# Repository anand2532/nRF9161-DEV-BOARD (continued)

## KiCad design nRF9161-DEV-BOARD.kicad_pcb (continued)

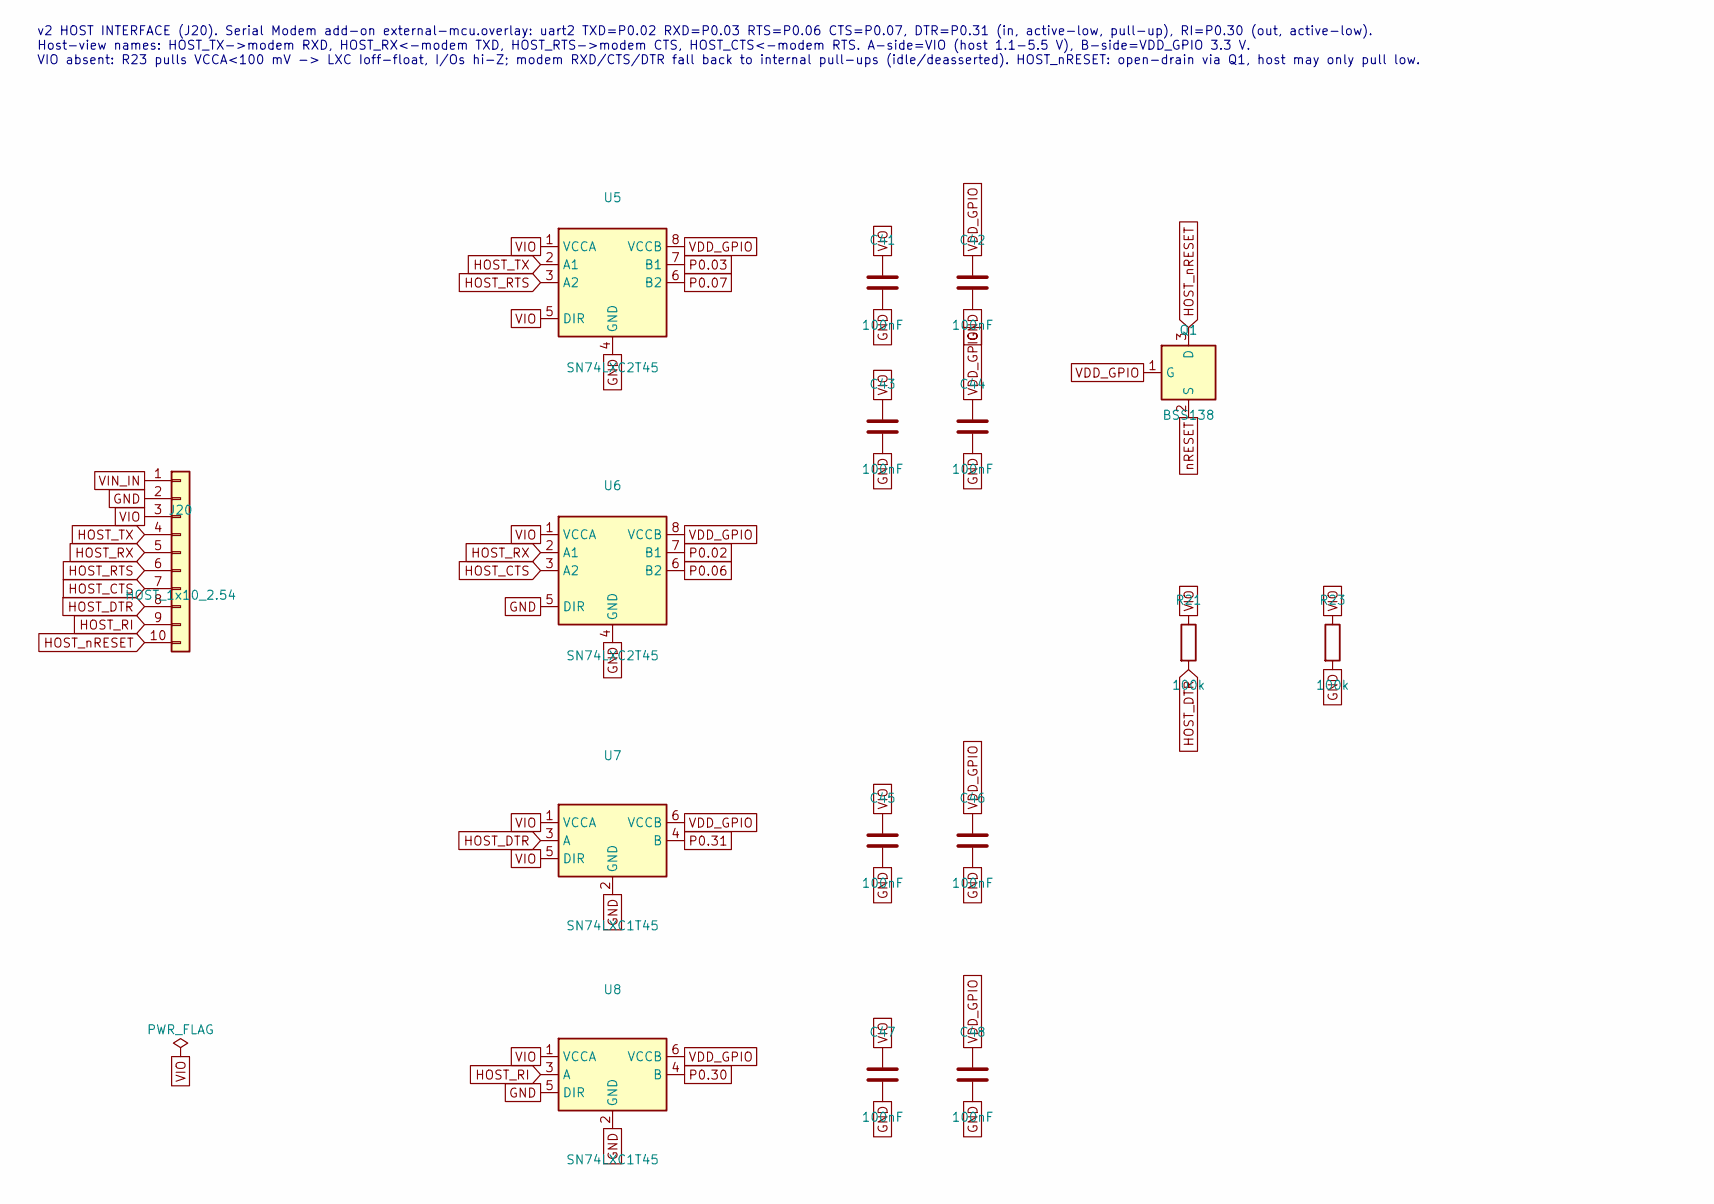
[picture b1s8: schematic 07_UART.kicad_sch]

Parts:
C41, C42, C43, C44, C45, C46, C47, C48: 100nF; C_0402_1005Metric; MPN CL05B104KO5NNNC; LCSC C1525
J20: HOST_1x10_2.54; PinHeader_1x10_P2.54mm_Vertical; MPN 2.54-1*10P; LCSC C57369
Q1: BSS138; SOT-23; MPN BSS138; LCSC C52895
R21, R23: 100k; R_0402_1005Metric; MPN 0402WGF1003TCE; LCSC C25741
U5, U6: SN74LXC2T45; VSSOP-8_2.3x2mm_P0.5mm; MPN SN74LXC2T45DCUR; LCSC C5217891
U7, U8: SN74LXC1T45; SOT-23-6; MPN SN74LXC1T45DBVR; LCSC C4364198

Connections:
GND: C41.2, C42.2, C43.2, C44.2, C45.2, C46.2, C47.2, C48.2, J20.2, R23.2, U5.4 (GND), U6.4 (GND), U6.5 (DIR), U7.2 (GND), U8.2 (GND), U8.5 (DIR); also elsewhere on the board
HOST_CTS: J20.7, U6.3 (A2)
HOST_DTR: J20.8, R21.2, U7.3 (A)
HOST_RI: J20.9, U8.3 (A)
HOST_RTS: J20.6, U5.3 (A2)
HOST_RX: J20.5, U6.2 (A1)
HOST_TX: J20.4, U5.2 (A1)
HOST_nRESET: J20.10, Q1.3 (D)
P0.02: U6.7 (B1); also elsewhere on the board
P0.03: U5.7 (B1); also elsewhere on the board
P0.06: U6.6 (B2); also elsewhere on the board
P0.07: U5.6 (B2); also elsewhere on the board
P0.30: U8.4 (B); also elsewhere on the board
P0.31: U7.4 (B); also elsewhere on the board
VDD_GPIO: C42.1, C44.1, C46.1, C48.1, Q1.1 (G), U5.8 (VCCB), U6.8 (VCCB), U7.6 (VCCB), U8.6 (VCCB); also elsewhere on the board
VIN_IN: J20.1; also elsewhere on the board
VIO: C41.1, C43.1, C45.1, C47.1, J20.3, R21.1, R23.1, U5.1 (VCCA), U5.5 (DIR), U6.1 (VCCA), U7.1 (VCCA), U7.5 (DIR), U8.1 (VCCA)
nRESET: Q1.2 (S); also elsewhere on the board

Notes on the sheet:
v2 HOST INTERFACE (J20). Serial Modem add-on external-mcu.overlay: uart2 TXD=P0.02 RXD=P0.03 RTS=P0.06 CTS=P0.07, DTR=P0.31 (in, active-low, pull-up), RI=P0.30 (out, active-low). Host-view names: HOST_TX->modem RXD, HOST_RX<-modem TXD, HOST_RTS->modem CTS, HOST_CTS<-modem RTS. A-side=VIO (host 1.1-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

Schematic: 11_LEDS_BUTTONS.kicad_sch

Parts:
D4: Green LED; LED_0603_1608Metric; MPN LTST-C191KGKT; LCSC C125098
R10: 1k; R_0402_1005Metric; MPN 0402WGF1001TCE; LCSC C11702

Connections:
GND: D4.2 (A); also elsewhere on the board
LED1_A: D4.1 (K), R10.2
P0.00: R10.1; also elsewhere on the board

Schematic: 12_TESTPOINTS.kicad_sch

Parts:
TP13: VDD_GPIO; TestPoint_Pad_D1.5mm
TP14: VDD_nRF; TestPoint_Pad_D1.5mm
TP15: VIN; TestPoint_Pad_D1.5mm
TP16: GND; TestPoint_Pad_D1.5mm
TP17: ENABLE; TestPoint_Pad_D1.5mm

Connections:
ENABLE: TP17.1; also elsewhere on the board
GND: TP16.1; also elsewhere on the board
VDD_GPIO: TP13.1; also elsewhere on the board
VDD_nRF: TP14.1; also elsewhere on the board
VIN: TP15.1; also elsewhere on the board

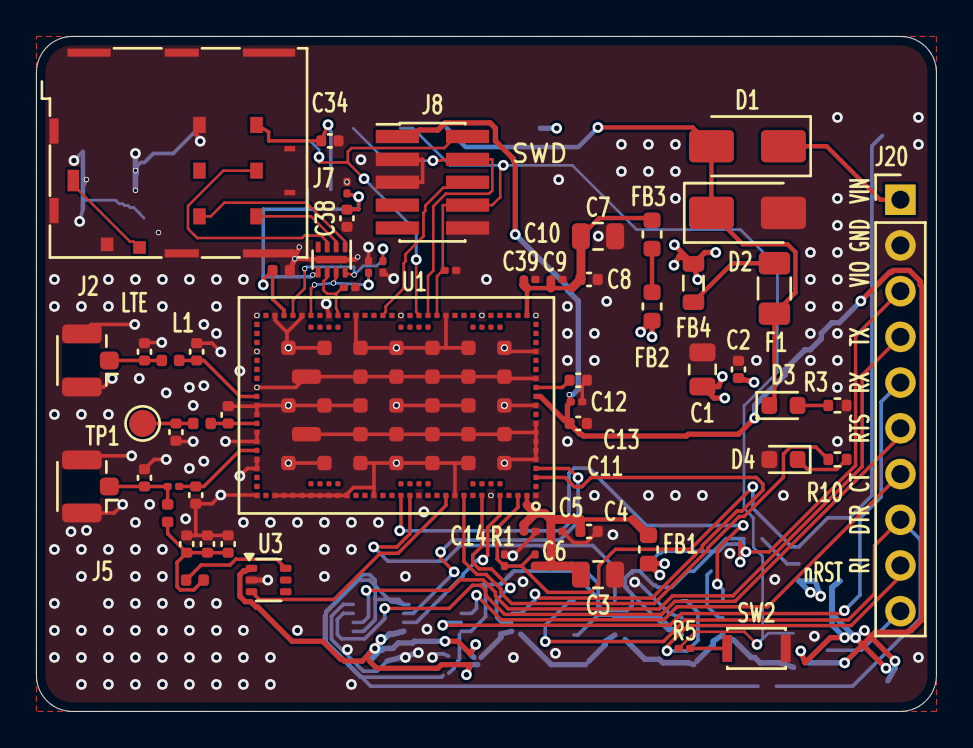
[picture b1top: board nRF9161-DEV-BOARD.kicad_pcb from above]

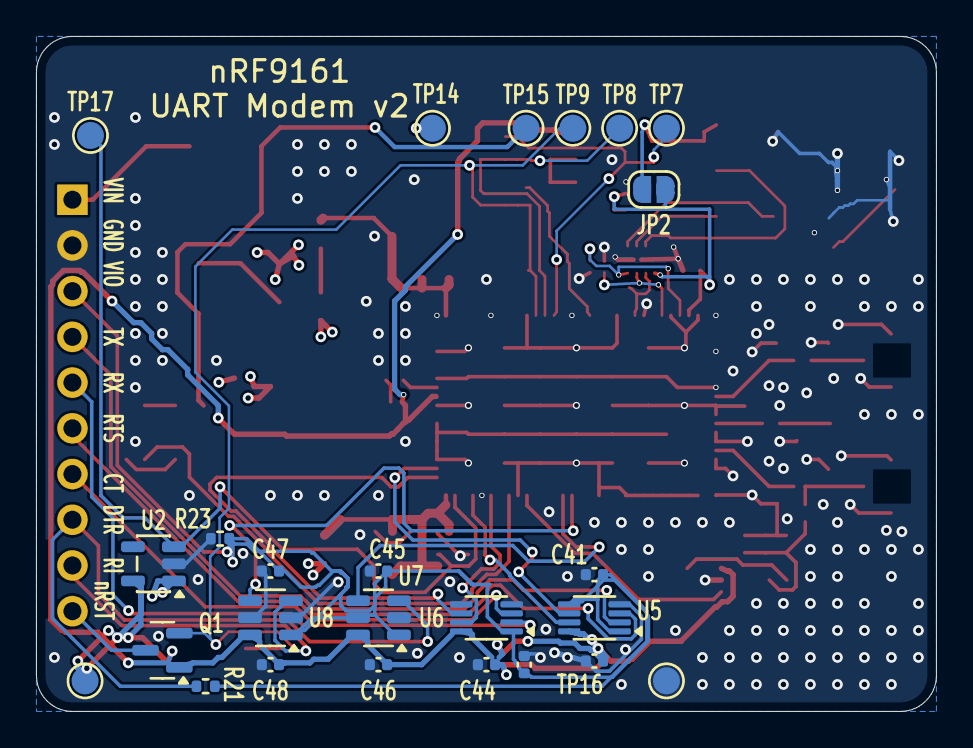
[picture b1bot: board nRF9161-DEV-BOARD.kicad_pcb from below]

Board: 4 copper layers, 50.0 x 37.5 mm, 84 parts (25 on the bottom side), 51 nets.

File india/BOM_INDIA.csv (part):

Ref,Qty/board,Value,Package,MPN,LCSC,V1 vendor,V1 URL,V1 INR/unit,V1 stock,V1 match,V2 vendor,V2 URL,V2 INR/unit,V2 stock,V2 match,Exact in-stock INR/board,Notes
U1,1,nRF9161 SiP,LGA 16.0x10.5,NRF9161-LACA-R7,C21547412,LionCircuits,https://www.lioncircuits.com/parts/NRF9161-LACA-R7,3745.04,In Stock (ships 7-10 d),exact,,,,,,3745.04,Not on Robu (only nRF9151-DK). Also try mouser.in / digikey.in.
U2,1,TLV73333P,SOT-23-5,TLV73333PDBVR,C134139,Robu,https://robu.in/product/tlv73333pdbvr-texas-instruments-300m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,20.0,In Stock,exact,,,,,,20.0,
U3,1,TPS22919,SC-70-6,TPS22919DCKR,C2149796,LionCircuits,https://www.lioncircuits.com/parts/TPS22919DCKR,29.31,In Stock (ships 7-10 d),exact,,,,,,29.31,Not on Robu. LionCircuits price tiers start at 10 pcs (₹19.62).
U4,1,TPD3F303,USON-8 DPV,TPD3F303DPVR,C2865991,LionCircuits,https://www.lioncircuits.com/parts/TPD3F303DPVR,200.1,In Stock (ships 7-10 d),exact,,,,,,200.1,Not on Robu.
"U5,U6",2,SN74LXC2T45,VSSOP-8,SN74LXC2T45DCUR,C5217891,Robu,https://robu.in/product/sn74lxc2t45dcur-texas-instruments-1-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,65.0,In Stock,exact,,,,,,130.0,
"U7,U8",2,SN74LXC1T45,SOT-23-6,SN74LXC1T45DBVR,C4364198,Robu,https://robu.in/product/sn74lxc1t45dbvr-texas-instruments-1-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,31.0,In Stock,exact,,,,,,62.0,
Q1,1,BSS138,SOT-23,BSS138 (onsemi),C52895,LionCircuits,https://www.lioncircuits.com/parts/BSS138,38.95,In Stock (ships 7-10 d),exact,Robu,https://robu.in/product/bss138-slkor-50v-220ma-3-5%cf%8910v2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,2.45,In Stock,equivalent,38.95,"Robu has Slkor BSS138 (same MPN, other maker). Lion manufacturer not verified on page."
C1,1,10uF 16V X5R,0805,CL21A106KOQNNNE,C1713,Robu,https://robu.in/product/cl21a106koqnnne-samsung-electro-mech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,1.5,In Stock,exact,LionCircuits,https://www.lioncircuits.com/parts/CL21A106KOQNNNE,14.72,In Stock,exact,1.5,
"C2,C30,C33,C41-C48",11,100nF,0402,CL05B104KO5NNNC,C1525,Robu,https://robu.in/product/cl05b104ko5nnnc-samsung-electro-mech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,0.1,In Stock,exact,,,,,,1.1,
"C3,C7",2,47uF 10V X5R,0805,GRM21BR61A476ME15L,C124129,Robu,https://robu.in/product/grm21br61a476me15k-murata-power-solu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,4.63,In Stock,equivalent,Robu (exact ME15L),https://robu.in/product/grm21br61a476me15l-murata-smd-multil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,11.0,Out of Stock,exact,,"ME15K = same part, different reel packaging suffix. Exact ME15L is OOS on Robu and LionCircuits (₹75.19 OOS)."
"C4,C8,C11,C13",4,4.7uF 10V X5R,0402,GRM155R61A475MEAAD,C335105,Robu,https://robu.in/product/grm155r61a475meaad-murata-smd-multil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,1.59,In Stock,exact,Robu,https://robu.in/product/cl05a475kp5nrnc-samsung-cap-ceramic-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,0.36,In Stock,equivalent,6.36,Backup: Samsung CL05A475KP5NRNC
"C5,C9,C12,C14",4,100nF 10V X5R,0201,GRM033R61A104KE15D,C76934,Robu,https://robu.in/product/grm033r61a104ke15d-murata-smd-multil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,1.2,In Stock,exact,Robu,https://robu.in/product/cl03a104ko3nnnc-samsang-16v-100nf-x5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,0.11,In Stock,equivalent,4.8,Backup: Samsung CL03A104KO3NNNC
"C6,C10",2,15pF 25V C0G,0201,GJM0335C1E150JB01D,C710722,LionCircuits,https://www.lioncircuits.com/parts/GJM0335C1E150JB01D,12.74,In Stock,exact,Robu,https://robu.in/product/grm0335c1h150ga01d-murata-electronic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,0.35,In Stock,equivalent,25.48,Robu backup GRM0335C1H150GA01D (not high-Q GJM).
C27,1,100pF C0G,0201,GRM0335C1H101JA01D,C76922,Robu,https://robu.in/product/grm0335c1h101ja01d-murata-cap-cerami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,0.68,In Stock,exact,,,,,,0.68,
C28,1,100pF,0402,GRM1555C1H101JA01D,C77177,Robu,https://robu.in/product/grm1555c1h101ja01d-murata-cap-cerami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,0.12,In Stock,exact,,,,,,0.12,
C29,1,10nF,0402,CL05B103KB5NNNC,C15195,Robu,https://robu.in/product/cl05b103kb5nnnc-samsung-electro-mech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,1.56,In Stock,exact,,,,,,1.56,
C34,1,220nF,0402,CL05B224KO5NNNC,C16772,Robu,https://robu.in/product/cl05b224ko5nnnc-samsung-electro-mech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,1.49,In Stock,exact,,,,,,1.49,
C35-C38,4,22pF C0G,0201,GRM0335C1H220JA01D,C76924,Robu,https://robu.in/product/grm0335c1h220ja01d-murata-cap-cerami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,0.68,In Stock,exact,,,,,,2.72,
C40,1,100nF 10V X7R,0402,GRM155R71A104KA01D,C71687,Robu,https://robu.in/product/grm155r71a104ka01d-murata-cap-cerami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,0.12,In Stock,exact,,,,,,0.12,
D1,1,SS34,SMA,SS34 (MDD),C8678,Robu,https://robu.in/product/ss34-mdd-40v-independent-3a-550mv3a-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,7.0,In Stock,exact,Robu,https://robu.in/product/ss34-slkor-40v-500mv3a-3a-smado-214a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,3.79,In Stock,equivalent,7.0,"Backup is Slkor SS34 (same MPN, other maker)."
D2,1,SMAJ5.0A,SMA,SMAJ5.0A,C10758,Robu,https://robu.in/product/smaj5-0a-littelfuse-smaj5-0a-tvs-dio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,21.0,In Stock,exact,LionCircuits,https://www.lioncircuits.com/parts/SMAJ5.0A,56.08,In Stock,exact,21.0,Robu part is Littelfuse (BOM maker RUILON); same MPN.
"D3,D4",2,Green LED,0603,LTST-C191KGKT,C125098,Robu,https://robu.in/product/ltst-c191kgkt-lite-on-20ma-35mcd-wat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,2.1,In Stock,exact,LionCircuits,https://www.lioncircuits.com/parts/LTST-C191KGKT,17.05,In Stock,exact,4.2,
F1,1,2A fuse,1206,0468002.NRHF,C187611,LionCircuits,https://www.lioncircuits.com/parts/0468002.NRHF,187.64,In Stock (ships 7-10 d),exact,Robu,https://robu.in/product/0466002-nr-littelfuse-0466002-nr-fus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,11.0,In Stock,equivalent,187.64,Robu backup 0466002.NR is very-fast-acting 2A 63V 1206 (0468 is slow-blow): check inrush.
FB1-FB3,3,BLM18KG221SN1,0603,BLM18KG221SN1D,C88980,LionCircuits,https://www.lioncircuits.com/parts/BLM18KG221SN1D,12.74,In Stock,exact,Robu,https://robu.in/product/blm18eg221sn1d-murata-ferrite-beads-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,1.2,In Stock,equivalent,38.22,Exact on Robu is OOS; BLM18EG221SN1D is 220R/2A.
FB4,1,BLM21PG221SN1,0805,BLM21PG221SN1D,C85840,LionCircuits,https://www.lioncircuits.com/parts/BLM21PG221SN1D,14.02,In Stock,exact,Robu,https://robu.in/product/blm21pg221sh1d-murata-ferrite-beads-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,3.31,In Stock,equivalent,14.02,Exact on Robu (₹4.30) is OOS; SH1D = automotive grade of same bead.
FB5,1,BLM15HG102SN1,0402,BLM15HG102SN1D,C76889,LionCircuits,https://www.lioncircuits.com/parts/BLM15HG102SN1D,25.49,In Stock,exact,Robu,https://robu.in/product/blm15ag102sn1d-murata-electronics-65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,0.48,In Stock,equivalent,25.49,Robu AG variant has weaker GHz performance.
"L1,L2",2,0R,0402,0402WGF0000TCE,C17168,Robu,https://robu.in/product/0402wgf0000tce-uniohm-royal-ohm-62-5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,0.18,Out of Stock,exact,,,,,,,NO IN-STOCK INDIA SOURCE FOUND. Any 0402 0R jumper works; try mouser.in/digikey.in.
L4,1,100nH,0402,LQW15ANR10J00D,C86130,LionCircuits,https://www.lioncircuits.com/parts/LQW15ANR10J00D,14.02,In Stock,exact,Robu,https://robu.in/product/lqg15hsr10j02d-murata-electronics-20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,0.29,In Stock,equivalent,14.02,"Robu backup LQG15HS is multilayer, lower Q than wire-wound LQW."
R1,1,10k,0201,RC0201FR-0710KL,C106225,Robu,https://robu.in/product/rc0201fr-0710kl-yageo-50mw-thick-fil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,0.08,In Stock,exact,,,,,,0.08,
"R3,R10",2,1k,0402,0402WGF1001TCE,C11702,Robu,https://robu.in/product/0402wgf1001tce-uniohm-royal-ohm-62-5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,0.19,In Stock,exact,,,,,,0.38,
R5,1,1k,0201,RC0201FR-071KL,C138165,Robu,https://robu.in/product/rc0201fr-071kl-yageo-res-thick-film-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,0.08,In Stock,exact,,,,,,0.08,
"R21,R23",2,100k,0402,0402WGF1003TCE,C25741,Robu,https://robu.in/product/0402wgf1003tce-uniohm-royal-ohm-62-5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,0.07,In Stock,exact,,,,,,0.14,
"J2,J5",2,U.FL,U.FL,U.FL-R-SMT-1(10),C88373,LionCircuits,https://www.lioncircuits.com/parts/U.FL-R-SMT-1%2810%29,212.84,In Stock,exact,Robu,https://robu.in/product/u-fl-r-smt-180-hirose-1-inner-pin-ip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,18.0,In Stock,equivalent,425.68,"Robu (80) variant = same footprint, different packaging."
J7,1,nano-SIM,SF72S006,SF72S006VBDR2500,C2977286,LionCircuits,https://www.lioncircuits.com/parts/SF72S006VBDR2500,282.93,In Stock (ships 7-10 d),exact,,,,,,282.93,Not on Robu.
J8,1,SWD 2x5 1.27,SMD,FTSH-105-01-L-DV-K,C5155080,LionCircuits,https://www.lioncircuits.com/parts/FTSH-105-01-L-DV-K,155.75,In Stock (ships 7-10 d),exact,Robu,https://robu.in/product/1-month-warranty-922/,8.0,In Stock,equivalent,155.75,Robu XUNPU header has no -K shroud; check footprint.
J20,1,1x10 2.54,THT,2.54-1*10P (BOOMELE),C57369,Robu,https://robu.in/product/ds1021-1x10sf11-b-connfly-1x10-pin-2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,4.04,In Stock,equivalent,,,,,,,Any 1x10 2.54 mm header fits.
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
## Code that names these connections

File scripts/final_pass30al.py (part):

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Straight F.Cu from the y=22 island to the y=38 run hits no-net pads U1.51
and U1.73. Pad pitch is 0.50 mm with 0.30 mm pads (0.20 mm gaps); a 0.18 mm
track at 0.10 mm clearance cannot pass between them. A west F.Cu jog that
stays x>24.2 crosses MAGPIO/MIPI fanout and the ANT/AUX/GPS matching
(AUX horizontal reaches x=20.485). The west corridor also cannot hold a via.
One via is required to land.

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        f"**Pass delta (pass30al):** COEX0 landing, **{decision}**. Straight F.Cu from the "
        f"R4 via island (29.810, 22.000) to the y=38 run hits no-net U1.51 and U1.73; "
        f"0.50 mm pad pitch cannot be threaded, and a west F.Cu jog east of x=24.2 crosses "
        f"MAGPIO/MIPI and ANT/AUX/GPS (AUX reaches x=20.485). One 0.6/0.3 via at "
        f"(37.000, 30.500). Six 0.18 mm segments: B (31.110, 22.000)→(32.250, 22.000)→"
        f"(32.250, 30.500)→(37.000, 30.500), F (37.000, 30.500)→(37.000, 35.900)→"
        f"(38.750, 35.900)→(38.750, 37.250) onto U1.93 (same island as the y=38 run). "
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        f"{a.get('shorting_items')}/{a.get('clearance')}/{a.get('tracks_crossing')}/{a.get('hole_clearance')}. "
        f"hole_to_hole {b.get('hole_to_hole')}→{a.get('hole_to_hole')}. "
        f"GND islands {b.get('gnd_zone_islands')}→{a.get('gnd_zone_islands')} (waived). "
        f"No non-GND net gained an open. P0.15 still 42. VDD_GPIO polyline, DEC0 B.Cu bridge, "
        f"P0.10/P0.12 x=47.0 not ripped. No U1/header move. No y=44.60 pocket. No Gerbers. "
        f"Details: `reports/PASS30AL_SUMMARY.md`.\n\n"
    )
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
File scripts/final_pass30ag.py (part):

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    geos = defaultdict(list)  # (kind, layer, a, b or None, radius)
    for t in board.GetTracks():
        n = t.GetNetname()
        if not n.startswith("SIM_") and n not in ("P0.03", "P0.22", "nRESET", "VDD_GPIO"):
            continue
        if t.Type() == pcbnew.PCB_VIA_T:
            x, y = mm(t.GetPosition().x), mm(t.GetPosition().y)
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        rstc = audit.get("SIM_RST_C", {})
        summary["audit"] = {
            "SIM_RST_C_opens_before": before_nets.get("SIM_RST_C", 0),
            "SIM_RST_C_continuous": before_nets.get("SIM_RST_C", 0) == 0,
            "SIM_RST_C_islands_touching_slot": rstc.get("islands_touching_B_slot"),
            "why": (
                "The opened slot is a closed pocket on B.Cu. "
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                "SIM_RST's nearest B copper ends at x=78.25,y=43.80 (about 3.6 mm from the mouth) "
                "and the other island is U1.43 at (32.75, 26.75). "
                "SIM_CLK / SIM_IO / SIM_1V8 opens are the U1-to-filter gaps west of x≈78, not this slot. "
                "SIM_IO's F spine at x=84 crosses the slot on F.Cu only (east island); a via there "
                "would not reach U1.48."
            ),
            "nearest_SIM_RST": rst.get("nearest"),
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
